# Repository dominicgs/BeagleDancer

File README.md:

BeagleDancer
============

A Facedancer expansion board for the BeagleBone.  Most of the hard work was
done by Travis Goodspeed and Philippe Teuwen.  You can find their projects at
http://goodfet.sf.net and http://wiki.yobi.be/wiki/Raspdancer.

It's called "BeagleDancer" because it sounded better than "FaceBone".

Pins (Beagle name)
------------------
- 1) GND
- 3) 3.3V
- 5) 5V
- 11) USB OTG ID detect (UART4_RXD - gpio0[30])
- 13) Interrupt (UART4_TXD - gpio0[31])
- 15) GPX (GPIO1_16 - gpio1[16])
- 17) SPI0_CS0 (I2C1_SCL)
- 18) SPI0_D1 (I2C1_SDA)
- 21) SPI0_D0 (UART2_TXD)
- 22) SPI0_SCLK (UART2_RXD)
- 23) Reset (GPIO1_17 - gpio1[17])

Software
--------
These instructions have been tested ona  Debian image for the BeagleBone Black,
the image can be found on the eLinux site:
http://elinux.org/BeagleBoardDebian#Flasher

First install the prerequisites:
 $ apt-get install gcc make python-dev python-serial
 
Seconly, configure the pin multiplexes to allow access to the SPI device from
the operating system.  Detailed instructions are given in devicetree/README.md
You may want to add a udev rule to allow non-root access to the SPI device.

The next step is to download and build the SPI-Py module (GPL), it can be found
at https://github.com/lthiery/SPI-Py

Build instructions are as follows:
- $ git clone git://github.com/lthiery/SPI-Py.git
- $ cd SPI-Py
- $ python setup.py build
- $ sudo python setup.py install

Finally, we need to reset the MAX3421 chip using GPIO1_17.  As root:
- $ echo "48" > /sys/class/gpio/export
- $ echo "49" > /sys/class/gpio/export
- $ echo "30" > /sys/class/gpio/export
- $ echo "31" > /sys/class/gpio/export
- $ echo "out" > /sys/class/gpio/gpio49/direction
- $ echo "0" > /sys/class/gpio/gpio49/value
- $ echo "1" > /sys/class/gpio/gpio49/value

Licensing, etc
--------------
Copyright 2013 Dominic Spill <dominicgs@gmail.com>.

This program is free software; you can redistribute it and/or modify it under
the terms of the GNU General Public License V2 as published by the Free Software
Foundation.

Liability
---------
This program is distributed for educational purposes only and is no way suitable
for any particular application, especially commercial. There is no implied
suitability so use at your own risk!

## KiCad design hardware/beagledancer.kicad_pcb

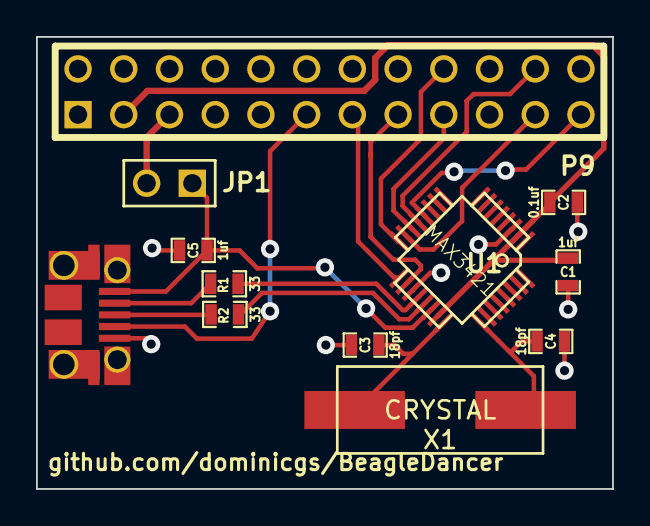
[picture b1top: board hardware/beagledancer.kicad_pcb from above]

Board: 2 copper layers, 32.0 x 25.1 mm, 12 parts (0 on the bottom side), 18 nets.

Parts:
C1, C5: 1uf; SM0603_Capa
C2: 0.1uf; SM0603_Capa
C3, C4: 18pf; SM0603_Capa
J1: USB-MICRO-B; GSG-USB-MICROB-FCI-10103594
JP1: JUMPER; PIN_ARRAY_2X1
P9: BeagleBone; pin_array_12x2
R1, R2: 33; SM0603_Resistor
U1: MAX3421
X1: CRYSTAL; HC49-US

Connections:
+3.3V: C1.1, C2.1, P9.3, U1.2, U1.23
+5V: JP1.2, P9.5
/D+: R2.1, U1.21
/D-: R1.1, U1.20
/RES: P9.23, U1.12
/VBCOMP: C5.1, J1.1, JP1.1, U1.22
/XI: C3.1, U1.24, X1.1
/XO: C4.1, U1.25, X1.2
GND: C1.2, C2.2, C3.2, C4.2, C5.2, J1.5, P9.1, U1.3, U1.19
GPX: P9.13, U1.17
INT: P9.15, U1.18
unnamed: J1.2, R1.2
unnamed: J1.3, R2.2
SPI0_CS0: P9.17, U1.14
SPI0_D0: P9.21, U1.15
SPI0_D1: P9.18, U1.16
SPI0_SCLK: P9.22, U1.13
USB_ID: J1.4, P9.11

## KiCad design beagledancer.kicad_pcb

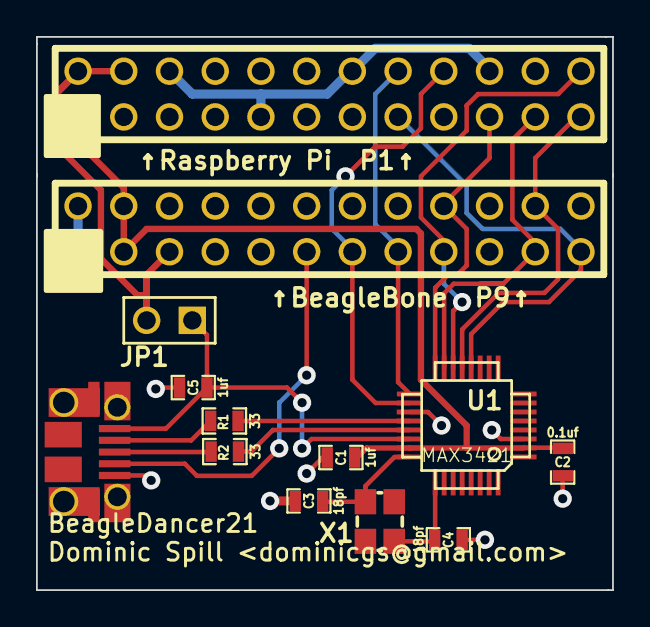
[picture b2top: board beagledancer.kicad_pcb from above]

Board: 2 copper layers, 32.0 x 30.7 mm, 13 parts (0 on the bottom side), 18 nets.

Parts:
C1, C5: 1uf; SM0603_Capa
C2: 0.1uf; SM0603_Capa
C3, C4: 18pf; SM0603_Capa
J1: USB-MICRO-B; GSG-USB-MICROB-FCI-10103594
JP1: JUMPER; PIN_ARRAY_2X1
P9: BeagleBone; pin_array_12x2
Pi1: Raspberry Pi; pin_array_12x2
R1, R2: 33; SM0603_Resistor
U1: MAX3421
X1: XTAL4PIN; GSG-XTAL3.2x2.5mm

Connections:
+3.3V: C1.1, C2.1, P9.3, P9.4, Pi1.1, U1.2, U1.23
+5V: JP1.2, P9.5, Pi1.2, Pi1.4
/D+: R2.1, U1.21
/D-: R1.1, U1.20
/RES: P9.23, Pi1.15, U1.12
/VBCOMP: C5.1, J1.1, JP1.1, U1.22
/XI: C3.1, U1.24, X1.1
/XO: C4.1, U1.25, X1.3
GND: C1.2, C2.2, C3.2, C4.2, C5.2, J1.5, P9.1, P9.2, Pi1.6, Pi1.9, Pi1.14, Pi1.20, U1.3, U1.19
GPX: P9.15, Pi1.16, U1.17
INT: P9.13, Pi1.18, U1.18
unnamed: J1.3, R2.2
unnamed: J1.2, R1.2
SPI_MISO: P9.21, Pi1.21, U1.15
SPI_MOSI: P9.18, Pi1.19, U1.16
SPI_SCLK: P9.22, Pi1.23, U1.13
SPI_SS: P9.17, Pi1.24, U1.14
USB_ID: J1.4, P9.11

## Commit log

2013-05-10 Initial commit of BeagleDancer design.
2013-05-11 Update based on feedback from Michael Ossmann (mossmann)
2013-05-11 Tweak layout to detect OTG pin status with GPIO pin
2013-05-11 Fix unreadable markdown
2013-05-11 More feedback
2013-05-11 Connect INT and GPX to GPIO pins on the Beagle.
2013-05-12 Fix MAX3421 size
2013-05-12 Tidy up 5V and 3.3V traces.
2013-05-12 Use bigger pads for the MAX3421 - as per land pattern.
2013-05-12 Swap C1/C2 to correct positions on schematic, named nets, ether tweaks.
2013-05-12 Add a header for the RPi.
2013-05-13 Add labels to silkscreen
2013-05-13 Adjust GND zone thermal relief to remove gaps around pin 1 of P9.
2013-05-13 Update silkscreens and GND zone for RPi header.
2013-05-14 Add part details to BOM.
2013-05-14 Add USB connector to BOM.
2013-06-09 Rearrange to add software portion of project
2013-06-10 Device tree config to get spidev1.0 working
2013-06-10 Working SPI and GPIO instructions
2013-06-10 Fix lists in readme files
2013-06-11 Fix paths for GPIO setup
2014-03-24 Change crystal to match FaceDancer
2014-03-24 Some minor tweaks to make everything fit properly.

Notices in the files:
beagledancer.kicad_pcb:
License: BSD 3-Clause, http://goodfet.sourceforge.net
